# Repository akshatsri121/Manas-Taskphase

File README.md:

# Project Manas: Final Taskphase

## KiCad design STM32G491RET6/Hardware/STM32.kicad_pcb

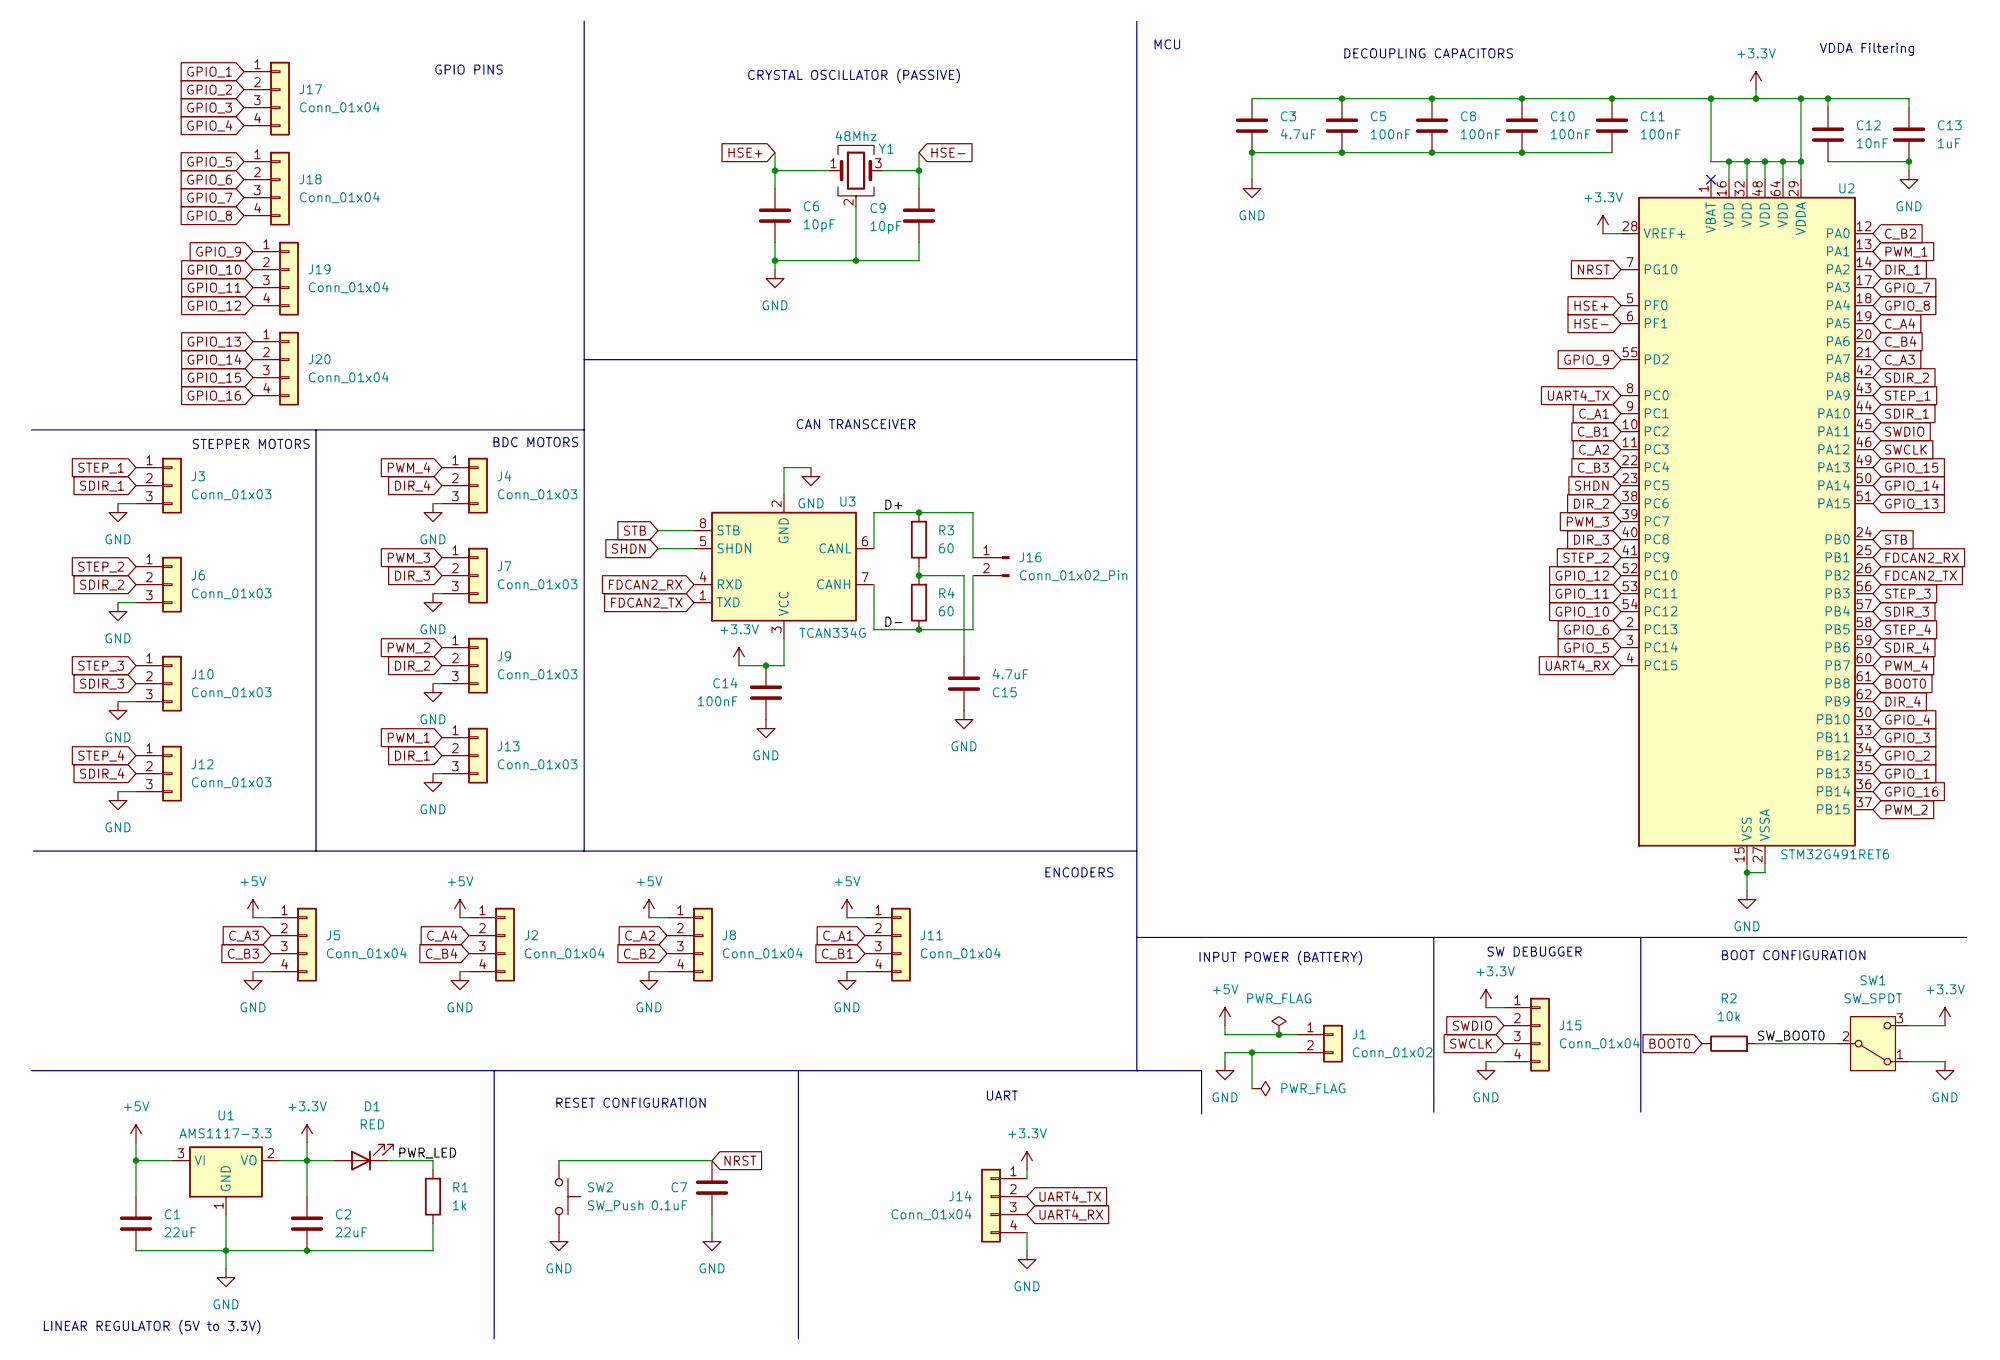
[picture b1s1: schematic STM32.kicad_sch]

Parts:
C1, C2: 22uF; C_0805_2012Metric
C3, C15: 4.7uF; C_0805_2012Metric
C5, C8, C10, C11, C14: 100nF; C_0805_2012Metric
C6, C9: 10pF; C_0805_2012Metric
C7: 0.1uF; C_0805_2012Metric
C12: 10nF; C_0805_2012Metric
C13: 1uF; C_0805_2012Metric
D1: RED; LED_0805_2012Metric
J1: Conn_01x02; JST_XH_B2B-XH-A_1x02_P2.50mm_Vertical
J2, J5, J8, J11, J14, J15: Conn_01x04; JST_XH_B4B-XH-A_1x04_P2.50mm_Vertical
J3, J4, J6, J7, J9, J10, J12, J13: Conn_01x03; JST_XH_B3B-XH-A_1x03_P2.50mm_Vertical
J16: Conn_01x02_Pin; JST_XH_B2B-XH-A_1x02_P2.50mm_Vertical
J17, J18, J19, J20: Conn_01x04; PinHeader_1x04_P2.54mm_Vertical
R1: 1k; R_0805_2012Metric
R2: 10k; R_0805_2012Metric
R3, R4: 60; R_0805_2012Metric
SW1: SW_SPDT; SW_Slide_SPDT_Straight_CK_OS102011MS2Q
SW2: SW_Push; SW_Tactile_SPST_NO_Straight_CK_PTS636Sx25SMTRLFS
U1: AMS1117-3.3; SOT-223-3_TabPin2
U2: STM32G491RET6; LQFP-64_10x10mm_P0.5mm
U3: TCAN334G; TSOT-23-8
Y1: 48Mhz; Crystal_SMD_3225-4Pin_3.2x2.5mm

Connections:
+3.3V: C2.1, C3.1, C5.1, C8.1, C10.1, C11.1, C12.1, C13.2, C14.2, D1.2 (A), J14.1, J15.1, SW1.3 (C), U1.2 (VO), U2.16 (VDD), U2.28 (VREF+), U2.29 (VDDA), U2.32 (VDD), U2.48 (VDD), U2.64 (VDD), U3.3 (VCC)
+5V: C1.1, J1.1, J2.1, J5.1, J8.1, J11.1, U1.3 (VI)
/D+: J16.1, R3.2, U3.6 (CANL)
/D-: J16.2, R4.1, U3.7 (CANH)
/PWR_LED: D1.1 (K), R1.2
/SW_BOOT0: R2.2, SW1.2 (B)
BOOT0: R2.1, U2.61 (PB8)
C_A1: J11.2, U2.9 (PC1)
C_A2: J8.2, U2.11 (PC3)
C_A3: J5.2, U2.21 (PA7)
C_A4: J2.2, U2.19 (PA5)
C_B1: J11.3, U2.10 (PC2)
C_B2: J8.3, U2.12 (PA0)
C_B3: J5.3, U2.22 (PC4)
C_B4: J2.3, U2.20 (PA6)
DIR_1: J13.2, U2.14 (PA2)
DIR_2: J9.2, U2.38 (PC6)
DIR_3: J7.2, U2.40 (PC8)
DIR_4: J4.2, U2.62 (PB9)
FDCAN2_RX: U2.25 (PB1), U3.4 (RXD)
FDCAN2_TX: U2.26 (PB2), U3.1 (TXD)
GND: C1.2, C2.2, C3.2, C5.2, C6.2, C7.2, C8.2, C9.2, C10.2, C11.2, C12.2, C13.1, C14.1, C15.2, J1.2, J2.4, J3.3, J4.3, J5.4, J6.3, J7.3, J8.4, J9.3, J10.3, J11.4, J12.3, J13.3, J14.4, J15.4, R1.1, SW1.1 (A), SW2.2, U1.1 (GND), U2.15 (VSS), U2.27 (VSSA), U2.31 (VSS), U2.47 (VSS), U2.63 (VSS), U3.2 (GND), Y1.2 (G), Y1.4 (G)
GPIO_1: J17.1, U2.35 (PB13)
GPIO_2: J17.2, U2.34 (PB12)
GPIO_3: J17.3, U2.33 (PB11)
GPIO_4: J17.4, U2.30 (PB10)
GPIO_5: J18.1, U2.3 (PC14)
GPIO_6: J18.2, U2.2 (PC13)
GPIO_7: J18.3, U2.17 (PA3)
GPIO_8: J18.4, U2.18 (PA4)
GPIO_9: J19.1, U2.55 (PD2)
GPIO_10: J19.2, U2.54 (PC12)
GPIO_11: J19.3, U2.53 (PC11)
GPIO_12: J19.4, U2.52 (PC10)
GPIO_13: J20.1, U2.51 (PA15)
GPIO_14: J20.2, U2.50 (PA14)
GPIO_15: J20.3, U2.49 (PA13)
GPIO_16: J20.4, U2.36 (PB14)
HSE+: C6.1, U2.5 (PF0), Y1.1
HSE-: C9.1, U2.6 (PF1), Y1.3
NRST: C7.1, SW2.1, U2.7 (PG10)
unnamed: C15.1, R3.1, R4.2
PWM_1: J13.1, U2.13 (PA1)
PWM_2: J9.1, U2.37 (PB15)
PWM_3: J7.1, U2.39 (PC7)
PWM_4: J4.1, U2.60 (PB7)
SDIR_1: J3.2, U2.44 (PA10)
SDIR_2: J6.2, U2.42 (PA8)
SDIR_3: J10.2, U2.57 (PB4)
SDIR_4: J12.2, U2.59 (PB6)
SHDN: U2.23 (PC5), U3.5 (SHDN)
STB: U2.24 (PB0), U3.8 (STB)
STEP_1: J3.1, U2.43 (PA9)
STEP_2: J6.1, U2.41 (PC9)
STEP_3: J10.1, U2.56 (PB3)
STEP_4: J12.1, U2.58 (PB5)
SWCLK: J15.3, U2.46 (PA12)
SWDIO: J15.2, U2.45 (PA11)
UART4_RX: J14.3, U2.4 (PC15)
UART4_TX: J14.2, U2.8 (PC0)

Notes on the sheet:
ENCODERS
STEPPER MOTORS
CAN TRANSCEIVER
INPUT POWER (BATTERY)
CRYSTAL OSCILLATOR (PASSIVE)
MCU
GPIO PINS
LINEAR REGULATOR (5V to 3.3V)
RESET CONFIGURATION
BOOT CONFIGURATION
VDDA Filtering
DECOUPLING CAPACITORS
SW DEBUGGER
UART
BDC MOTORS

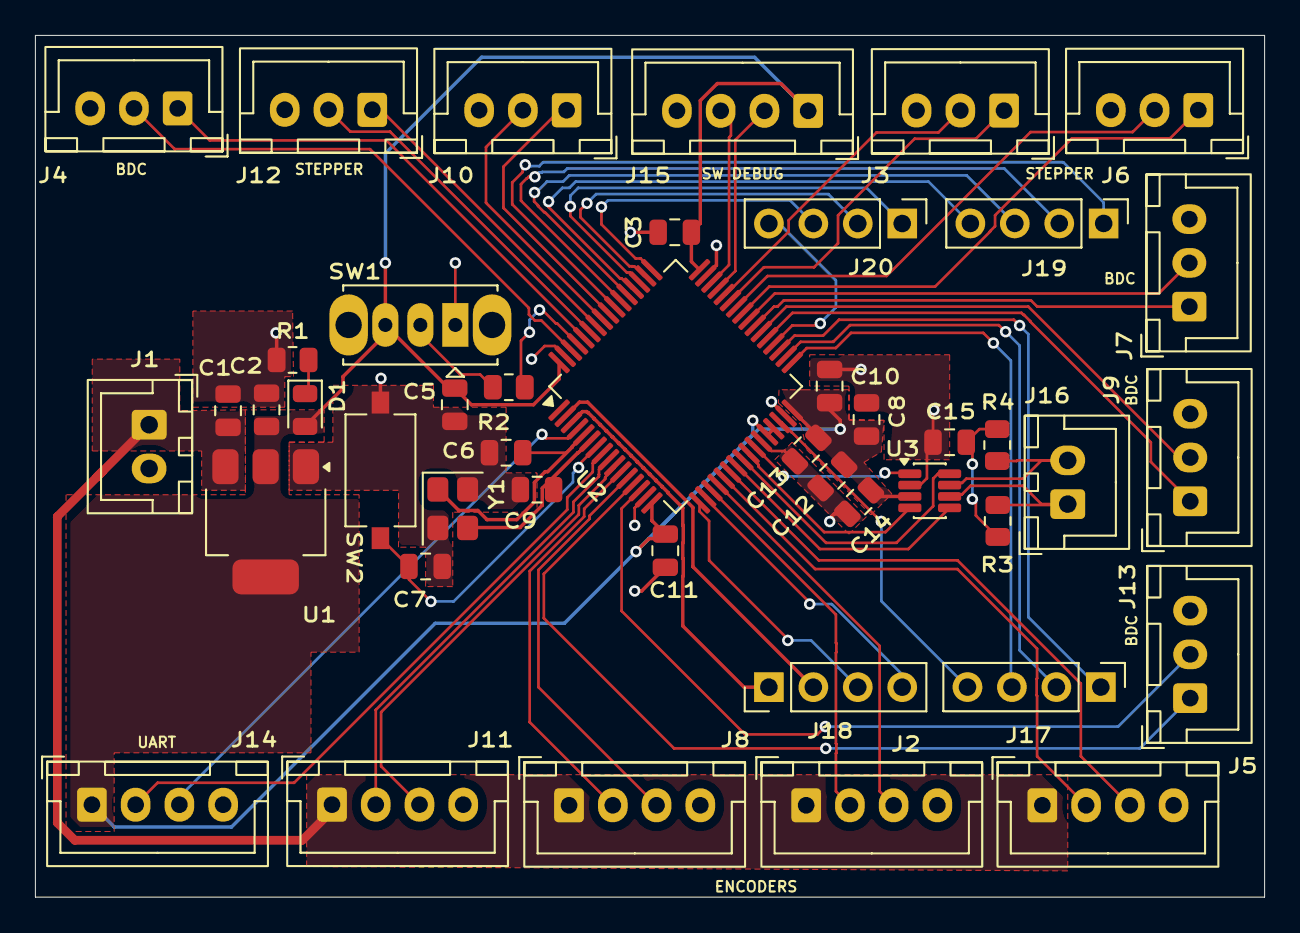
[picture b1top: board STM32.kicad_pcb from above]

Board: 2 copper layers, 70.2 x 49.2 mm, 45 parts (0 on the bottom side), 60 nets.

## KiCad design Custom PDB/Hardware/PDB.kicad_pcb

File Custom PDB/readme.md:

# Project Manas: Custom-Power-Distribution-Board

A custom high current Power Distribution Board (PDB) designed specifically for a differential drive robot. This board takes a raw battery input and cleanly steps it down into three isolated, logic level power rails (5V, 3.3V, 1.8V) while actively monitoring system wide power consumption in real time.

## Board Renders

## Key Features
* **Active Power Monitoring:** Integrated INA219 High side current and voltage monitor. Measures total current across a shunt resistor and reports data back to the microcontroller using I2C (SDA/SCL).
* **5V/3.3V Rail:** Used TPS54302 step down Buck Converter. Isolates power for 3.3V logic and sensors.
* **1.8V Rail:** Derived from the 3.3V rail using AP2112K-1.8 low dropout regulator (LDO) for sensitive components.
* **Mechanical Reliability:** 2-layer design with top and bottom ground planes for electromagnetic shielding, via stitched solid pours.

## System Architecture and Calculations

* **Input Voltage ($V_{in}$):** 12V (Battery Nominal), up to 16.8V (4S LiPo Max)
* **Switching Frequency ($f_{sw}$):** 400kHz
* **Internal Reference Voltage ($V_{ref}$):** 0.596V

### 1. Battery Voltage Sensing (V-Sense)
A voltage divider scales the main battery voltage down to a safe level for a standard 3.3V ADC.
* **Resistors:** R10 = 10kΩ, R1 = 2.2kΩ
* **Divider Ratio:**
  $$V_{ADC} = V_{BATT} \cdot \left(\frac{2.2}{10 + 2.2}\right) \approx V_{BATT} \cdot 0.1803$$
* **Calculated Thresholds:**
  * **@ 16.8V (4S LiPo Max):** 16.8V * 0.1803 = **3.03V** *(Safely below 3.3V limit)*
  * **@ 14.4V (Nominal):** 14.4V * 0.1803 = **2.59V**
  * **@ 12.0V (Discharged):** 12.0V * 0.1803 = **2.16V**

### 2. The 5V Rail
The TPS54302 steps down the 12V input by rapidly switching on and off. The exact 5V output is maintained by a resistor divider network (R3 and R4) that feeds a scaled-down voltage back to the chip's internal reference.
* **Calculated Output ($V_{out}$):**
  $$V_{out} = V_{ref} \cdot \left(1 + \frac{R_{top}}{R_{bot}}\right)$$
  $$V_{out} = 0.596 \cdot \left(1 + \frac{100}{13.3}\right) \approx 5.07\text{V}$$
* **Output Current Limit:** 3.0A (Maximum rating of the TPS54302)
* **Max Estimated Input Current:** ~1.39A *(Assuming a 12V input supplying 15W output at 90% converter efficiency)*

### 3. The 3.3V Sensor Rail
Similar to the 5V rail, the 3.3V rail uses a distinct resistor divider (R5 and R6) to program the output.
* **Calculated Output ($V_{out}$):**
  $$V_{out} = 0.596 \cdot \left(1 + \frac{100}{22.1}\right) \approx 3.29\text{V}$$
* **Output Current Limit:** 3.0A
* **Max Estimated Input Current:** ~0.92A *(Assuming a 12V input supplying 9.9W output at 90% converter efficiency)*

### 4. 1.8V Linear Regulator (AP2112K-1.8)
* **Input Voltage:** 3.3V (Fed directly from the 3.3V Buck rail)
* **Output Voltage:** 1.8V (Fixed)
* **Max Output Current:** 600mA

### 5. Power Monitor (INA219)
The INA219 monitors the total battery current utilizing a precision shunt resistor.
* **Shunt Resistor (R11):** 3mΩ (0.003Ω)
* **Max Measurable Voltage Drop:** ±320mV (Limit of the INA219 PGA)
* **Max Measurable Current:**
  $$I_{max} = \frac{320\text{mV}}{3\text{m}\Omega} = 106.67\text{A}$$

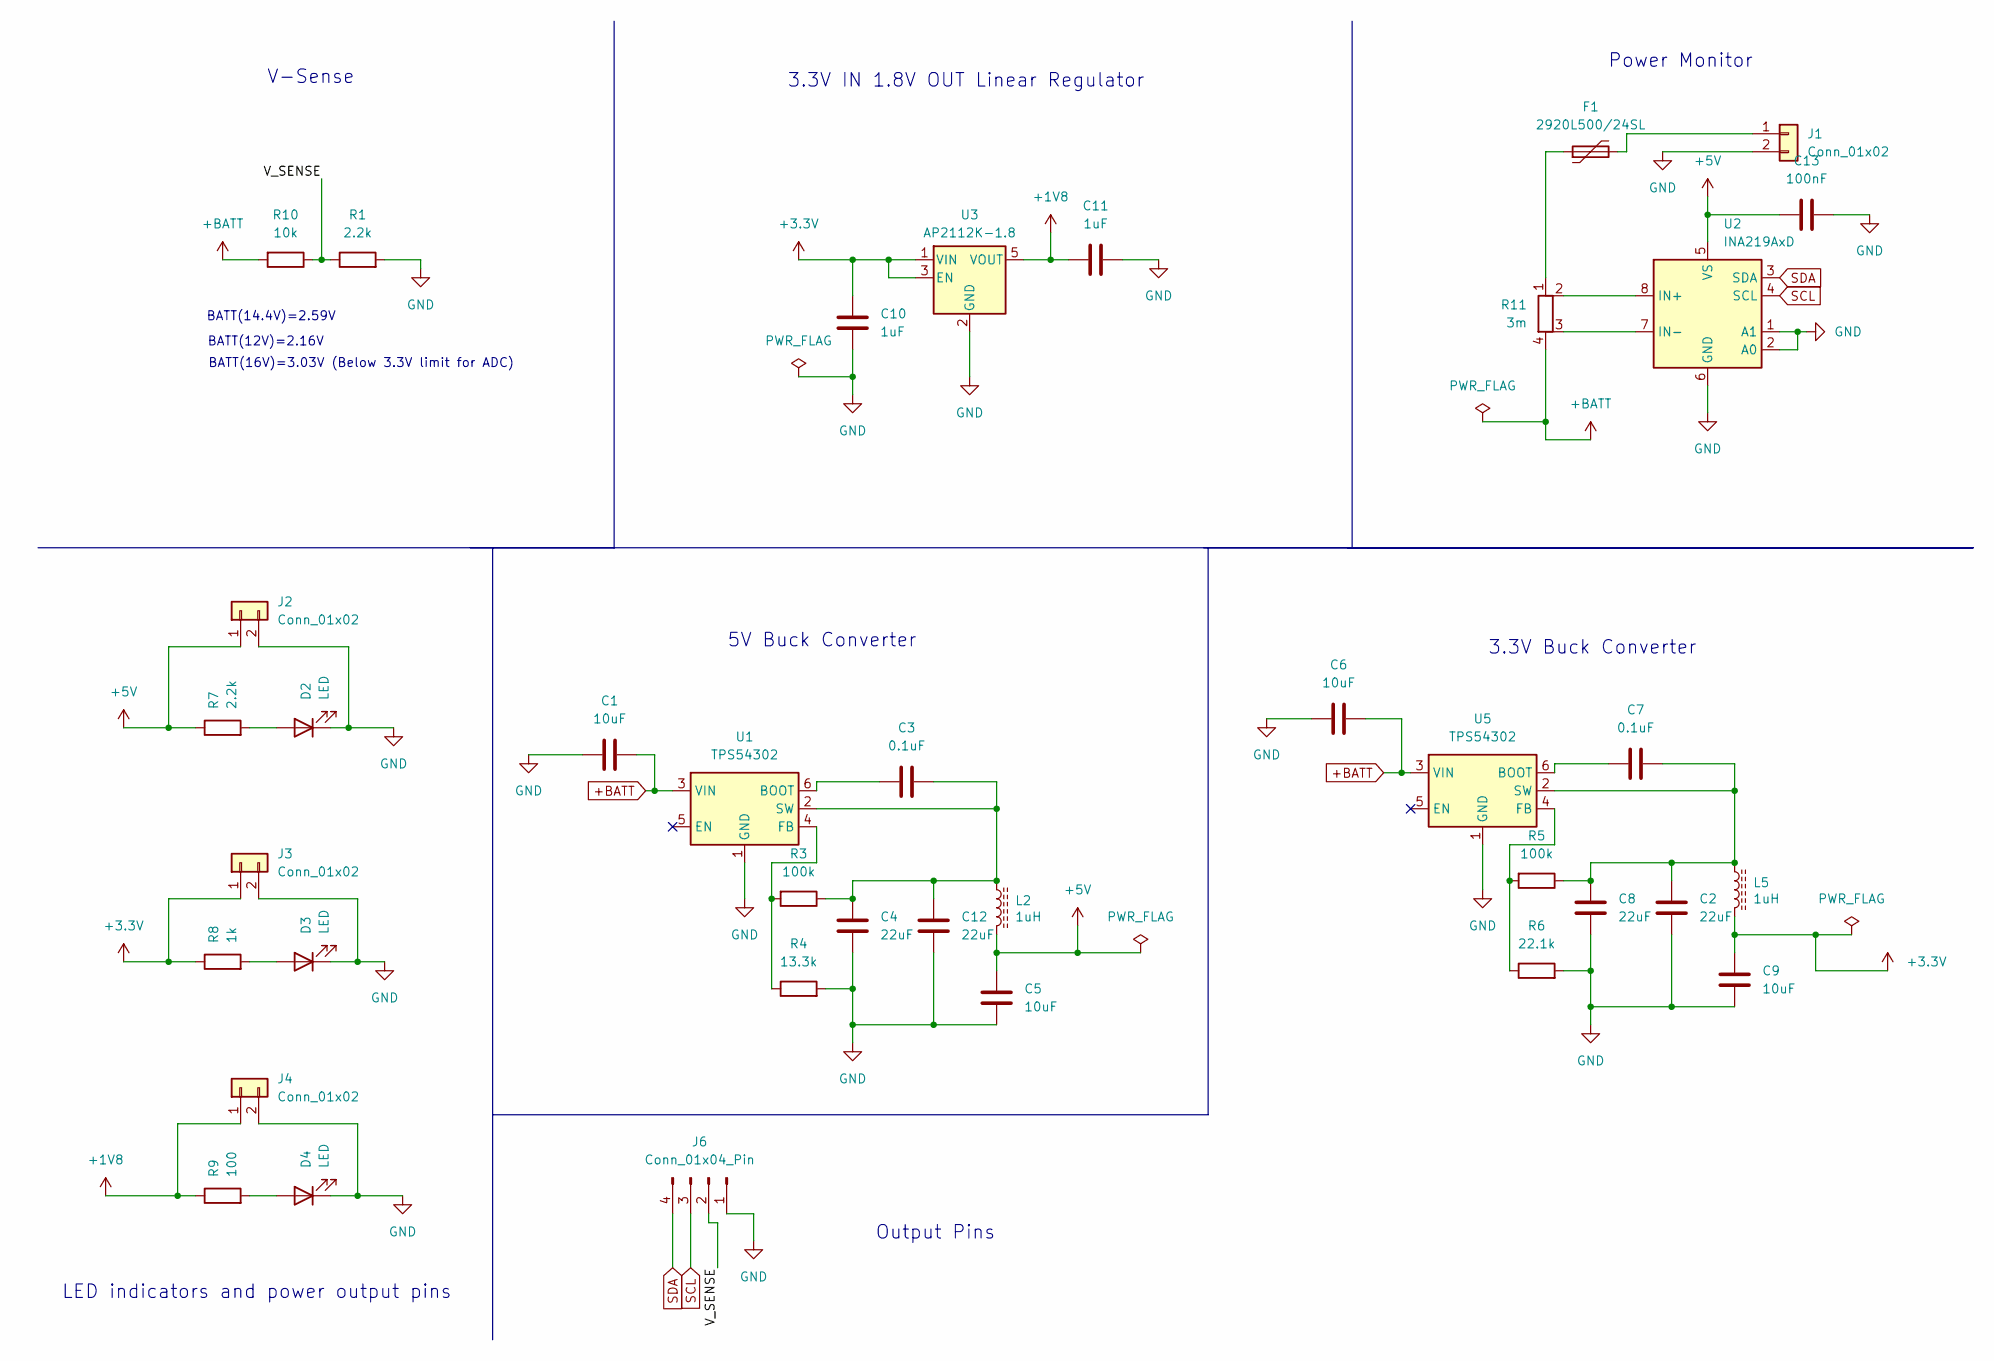
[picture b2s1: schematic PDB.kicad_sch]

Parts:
C1, C5, C6, C9: 10uF; C_0805_2012Metric
C2, C4, C8, C12: 22uF; C_0805_2012Metric
C3, C7: 0.1uF; C_0805_2012Metric
C10, C11: 1uF; C_0805_2012Metric
C13: 100nF; C_0805_2012Metric
D2, D3, D4: LED; LED_0805_2012Metric
F1: 2920L500/24SL; Fuse_2920_7451Metric
J1: Conn_01x02; AMASS_XT30PW-F_1x02_P2.50mm_Horizontal
J2, J3, J4: Conn_01x02; Molex_Micro-Fit_3.0_43650-0215_1x02_P3.00mm_Vertical
J6: Conn_01x04_Pin; PinHeader_1x04_P2.54mm_Vertical
L2, L5: 1uH; L_1206_3216Metric
R1, R7: 2.2k; R_0805_2012Metric
R3, R5: 100k; R_0805_2012Metric
R4: 13.3k; R_0805_2012Metric
R6: 22.1k; R_0805_2012Metric
R8: 1k; R_0805_2012Metric
R9: 100; R_0805_2012Metric
R10: 10k; R_0805_2012Metric
R11: 3m; R_Shunt_Isabellenhuette_BVR4026
U1, U5: TPS54302; SOT-23-6
U2: INA219AxD; SOIC-8_3.9x4.9mm_P1.27mm
U3: AP2112K-1.8; SOT-23-5

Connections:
+1V8: C11.1, J4.1, R9.1, U3.5 (VOUT)
+3.3V: C9.2, C10.1, J3.1, L5.2, R8.1, U3.1 (VIN), U3.3 (EN)
+5V: C5.2, C13.1, J2.1, L2.2, R7.1, U2.5 (VS)
+BATT: C1.1, C6.1, R10.2, R11.4, U1.3 (VIN), U5.3 (VIN)
/V_SENSE: J6.2, R1.1, R10.1
GND: C1.2, C2.2, C4.2, C5.1, C6.2, C8.2, C9.1, C10.2, C11.2, C12.2, C13.2, D2.1 (K), D3.1 (K), D4.1 (K), J1.2, J2.2, J3.2, J4.2, J6.1, R1.2, R4.2, R6.2, U1.1 (GND), U2.1 (A1), U2.2 (A0), U2.6 (GND), U3.2 (GND), U5.1 (GND)
unnamed: D2.2 (A), R7.2
unnamed: D3.2 (A), R8.2
unnamed: D4.2 (A), R9.2
unnamed: F1.1, R11.1
unnamed: F1.2, J1.1
unnamed: C3.1, U1.6 (BOOT)
unnamed: R3.2, R4.1, U1.4 (FB)
unnamed: C3.2, C4.1, C12.1, L2.1, R3.1, U1.2 (SW)
unnamed: R11.2, U2.8 (IN+)
unnamed: R11.3, U2.7 (IN-)
unnamed: C7.1, U5.6 (BOOT)
unnamed: R5.2, R6.1, U5.4 (FB)
unnamed: C2.1, C7.2, C8.1, L5.1, R5.1, U5.2 (SW)
SCL: J6.3, U2.4 (SCL)
SDA: J6.4, U2.3 (SDA)

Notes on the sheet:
5V Buck Converter
3.3V Buck Converter
V-Sense
Output Pins
BATT(16V)=3.03V (Below 3.3V limit for ADC)
LED indicators and power output pins
Power Monitor
BATT(14.4V)=2.59V
3.3V IN 1.8V OUT Linear Regulator
BATT(12V)=2.16V

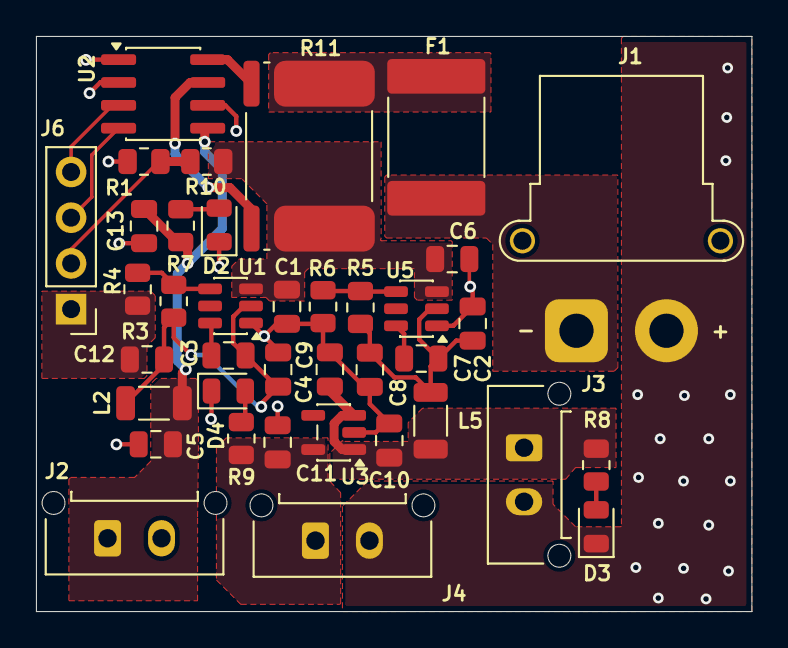
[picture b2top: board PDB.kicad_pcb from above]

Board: 2 copper layers, 39.8 x 31.9 mm, 38 parts (0 on the bottom side), 21 nets.

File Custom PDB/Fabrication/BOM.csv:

"Reference","Qty","Value","DNP","Exclude from BOM","Exclude from Board","Footprint","Datasheet"
"C1,C5,C6,C9","4","10uF","","","","Capacitor_SMD:C_1206_3216Metric","~"
"C2,C12,C13,C14","4","47uF","","","","Capacitor_SMD:C_1206_3216Metric","~"
"C3,C7","2","0.1uF","","","","Capacitor_SMD:C_0805_2012Metric","~"
"C4,C8","2","22uF","","","","Capacitor_SMD:C_1206_3216Metric","~"
"C10,C11","2","1uF","","","","Capacitor_SMD:C_0805_2012Metric","~"
"D2,D3,D4","3","LED","","","","LED_SMD:LED_0805_2012Metric","~"
"F1","1","Polyfuse","","","","Fuse:Fuse_1812_4532Metric","~"
"H1,H2,H3","3","MountingHole","","Excluded from BOM","","MountingHole:MountingHole_2.1mm","~"
"J1,J2,J3,J4,J5","5","Conn_01x02","","","","Connector_PinHeader_2.54mm:PinHeader_1x02_P2.54mm_Vertical","~"
"L2,L5","2","1uH","","","","Inductor_SMD:L_1206_3216Metric","~"
"L3","1","10uH","","","","Inductor_SMD:L_6.3x6.3_H3","~"
"L4","1","6.8uH","","","","Inductor_SMD:L_6.3x6.3_H3","~"
"Q1","1","Q_PMOS_GDS","","","","Package_SO:SOIC-8_3.9x4.9mm_P1.27mm","~"
"R2","1","10m","","","","Resistor_SMD:R_2512_6332Metric","~"
"R3,R5","2","100k","","","","Resistor_SMD:R_0805_2012Metric","~"
"R4","1","13.3k","","","","Resistor_SMD:R_0805_2012Metric","~"
"R6","1","22.1k","","","","Resistor_SMD:R_0805_2012Metric","~"
"R7","1","2.2k","","","","Resistor_SMD:R_0805_2012Metric","~"
"R8","1","1k","","","","Resistor_SMD:R_0805_2012Metric","~"
"R9","1","470","","","","Resistor_SMD:R_0805_2012Metric","~"
"U1,U5","2","TPS54302","","","","Package_TO_SOT_SMD:SOT-23-6","http://www.ti.com/lit/ds/symlink/tps54302.pdf"
"U2","1","INA219AxD","","","","Package_SO:SOIC-8_3.9x4.9mm_P1.27mm","http://www.ti.com/lit/ds/symlink/ina219.pdf"
"U3","1","AP2112K-1.8","","","","Package_TO_SOT_SMD:SOT-23-5","https://www.diodes.com/assets/Datasheets/AP2112.pdf"

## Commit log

2026-03-30 Schematic of the Printed Circuit Board
    Made using KiCad
2026-03-31 Datasheets for the components used
2026-03-31 Datasheets
    GIven datasheets for LDO, Buck Converter, Power Monitor
2026-03-31 Delete PDB.pdf
    Updated schematic with mounting holes
2026-03-31 Schematic of PDB
    Made with KiCad
    (Updated with mounting holes)
2026-04-01 Schematic of PDB
    fixed the schematic
2026-04-01 Add files via upload
    Added gerber and BOM file
2026-04-08 created a dedicated folder for PDB
2026-04-19 Schematic
2026-04-19 Create Hardware
2026-04-25 changed folder names
